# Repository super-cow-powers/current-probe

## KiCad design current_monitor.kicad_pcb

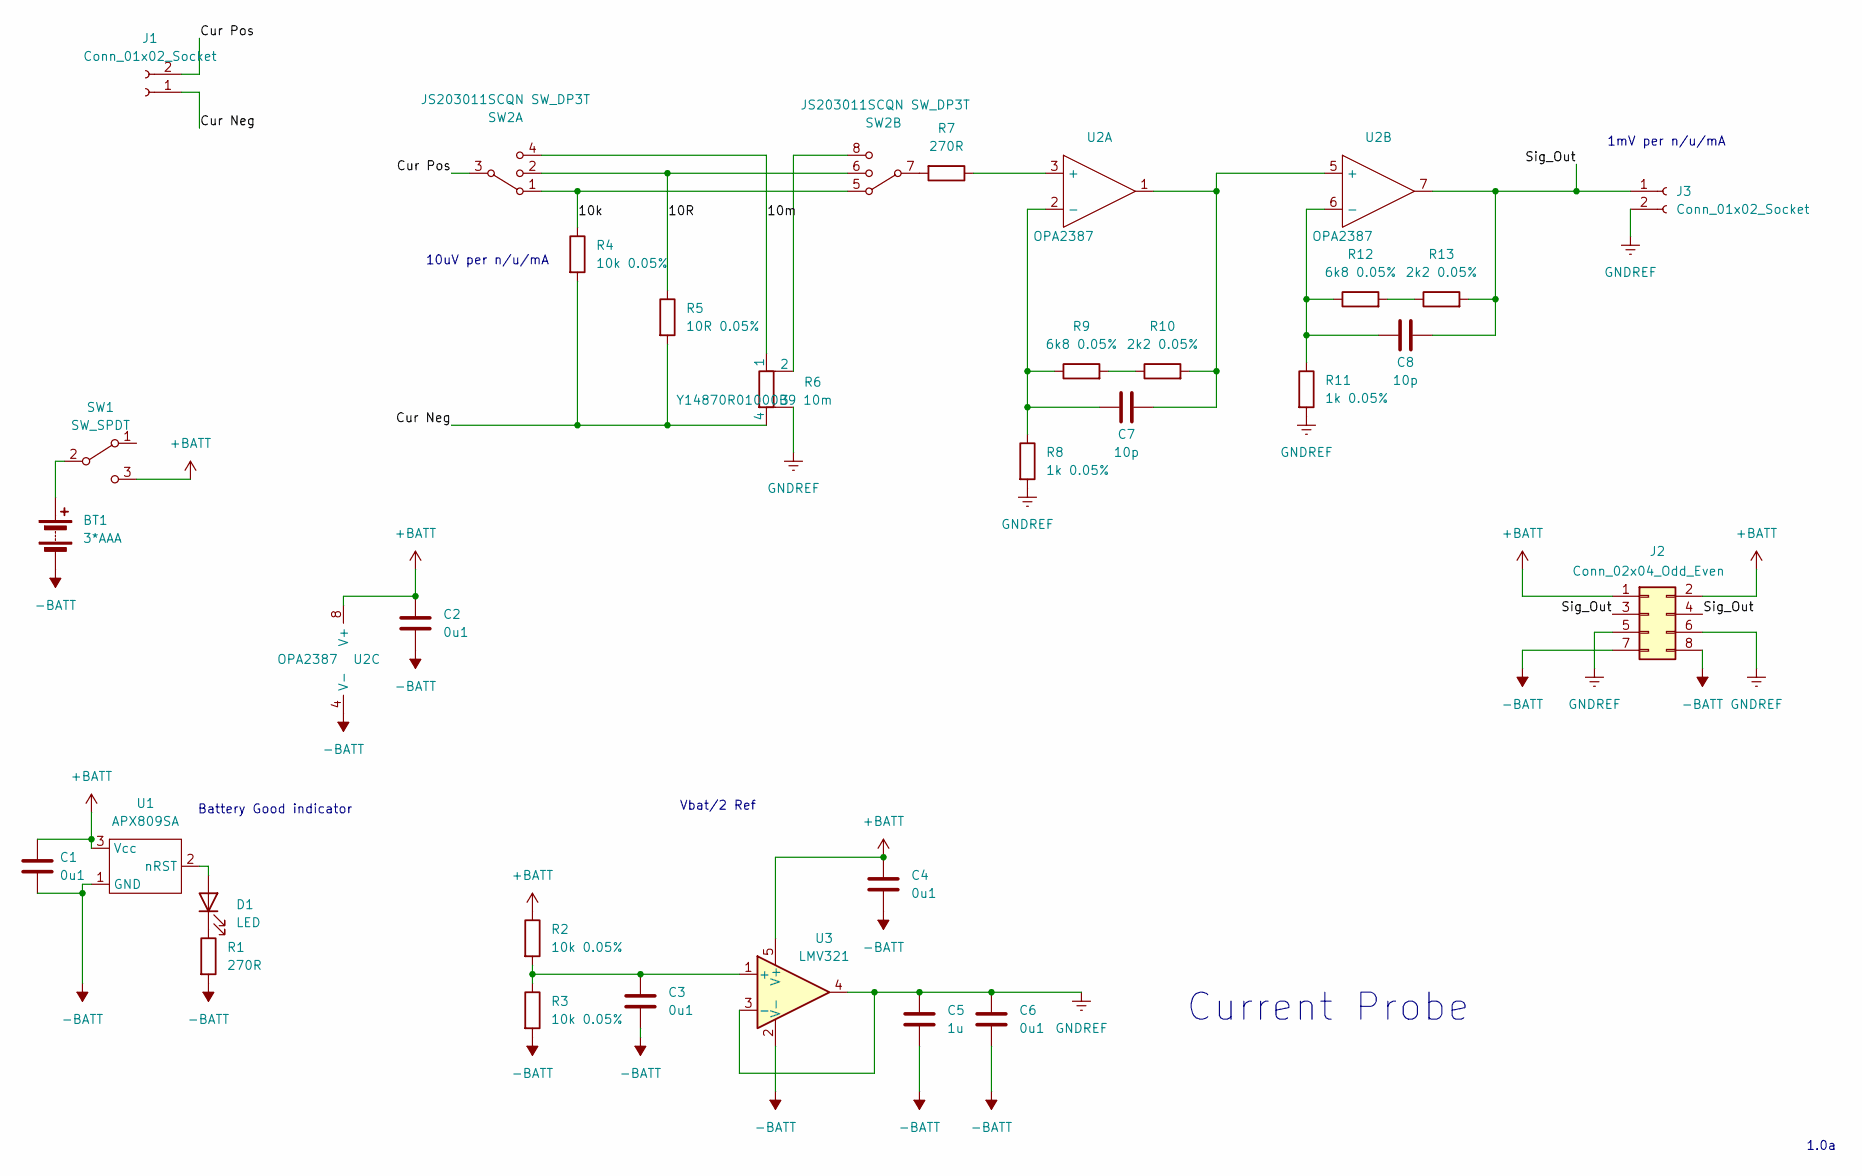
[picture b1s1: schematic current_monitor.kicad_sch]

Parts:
BT1: 3*AAA; PinHeader_1x02_P2.54mm_Vertical
C1, C2, C3, C4, C6: 0u1; C_0603_1608Metric_Pad1.08x0.95mm_HandSolder
C5: 1u; C_0603_1608Metric_Pad1.08x0.95mm_HandSolder
C7, C8: 10p; C_0603_1608Metric_Pad1.08x0.95mm_HandSolder
D1: LED; LED_D3.0mm
J1, J3: Conn_01x02_Socket; Dual M6 Banana
J2: Conn_02x04_Odd_Even; PinHeader_2x04_P1.27mm_Vertical_SMD
R1, R7: 270R; R_0603_1608Metric_Pad0.98x0.95mm_HandSolder
R2, R3, R4: 10k 0.05%; R_1206_3216Metric
R5: 10R 0.05%; R_1206_3216Metric
R6: Y14870R01000B9 10m; CSM2512S
R8, R11: 1k 0.05%; R_1206_3216Metric
R9, R12: 6k8 0.05%; R_1206_3216Metric
R10, R13: 2k2 0.05%; R_1206_3216Metric
SW1: SW_SPDT; SW_Slide_1P2T_CK_OS102011MS2Q
SW2: JS203011SCQN SW_DP3T; JS203011SCQN
U1: APX809SA; SOT-23
U2: OPA2387; VSSOP-8_3.0x3.0mm_P0.65mm
U3: LMV321; SOT-23-5

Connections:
+BATT: C1.1, C2.1, C4.1, J2.1, J2.2, R2.1, SW1.3 (C), U1.3 (Vcc), U2.8 (V+), U3.5 (V+)
-BATT: BT1.2 (-), C1.2, C2.2, C3.2, C4.2, C5.2, C6.2, J2.7, J2.8, R1.2, R3.2, U1.1 (GND), U2.4 (V-), U3.2 (V-)
/10R: R5.1, SW2.2, SW2.6
/10k: R4.1, SW2.1, SW2.5
/10m: R6.1, SW2.4
/Cur Neg: J1.1, R4.2, R5.2, R6.4
/Cur Pos: J1.2, SW2.3
/Sig_Out: C8.2, J2.3, J2.4, J3.1, R13.2, U2.7
GNDREF: C5.1, C6.1, J2.5, J2.6, J3.2, R6.3, R8.2, R11.2, U3.3 (-), U3.4
unnamed: BT1.1 (+), SW1.2 (B)
unnamed: D1.2 (A), U1.2 (nRST)
unnamed: D1.1 (K), R1.1
unnamed: R6.2, SW2.8
unnamed: R7.2, SW2.7
unnamed: R9.2, R10.1
unnamed: R12.2, R13.1
unnamed: R7.1, U2.3 (+)
unnamed: C7.1, R8.1, R9.1, U2.2 (-)
unnamed: C7.2, R10.2, U2.1, U2.5 (+)
unnamed: C8.1, R11.1, R12.1, U2.6 (-)
unnamed: C3.1, R2.2, R3.1, U3.1 (+)

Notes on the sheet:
Battery Good indicator
Vbat/2 Ref
10uV per n/u/mA
Current Probe
1mV per n/u/mA
1.0a

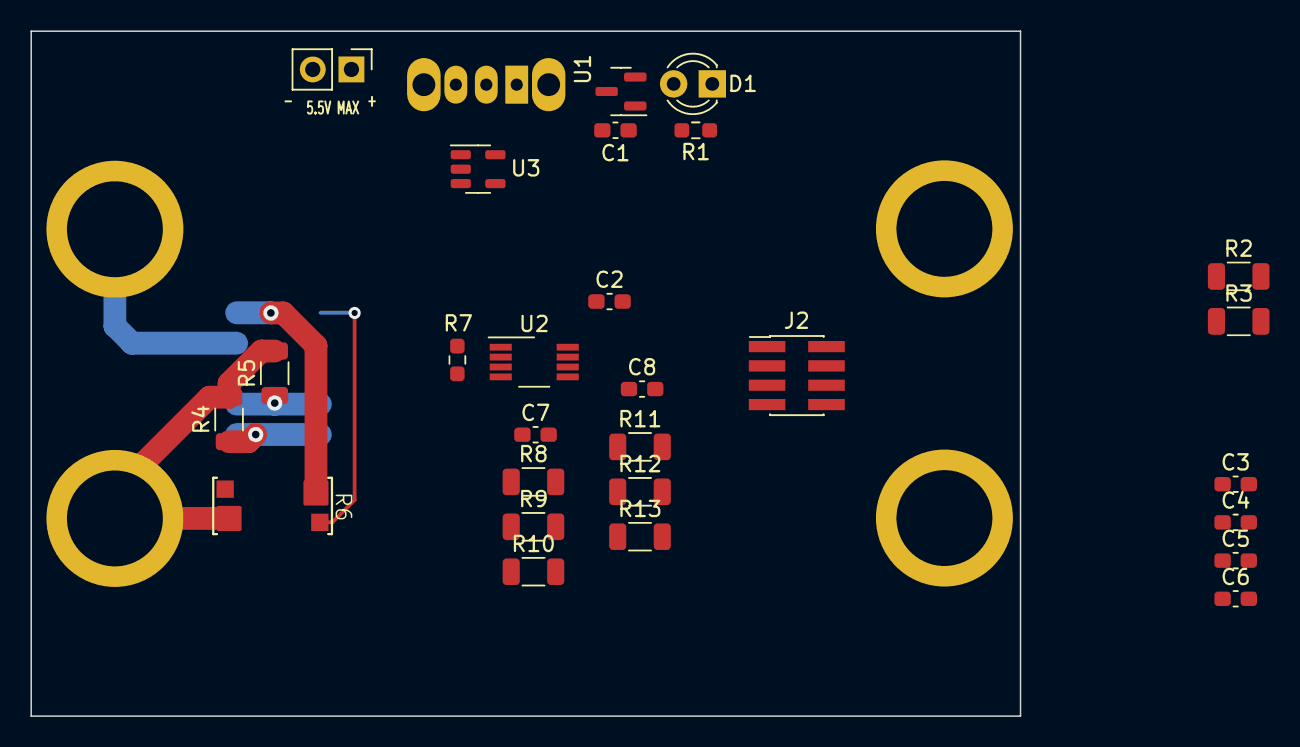
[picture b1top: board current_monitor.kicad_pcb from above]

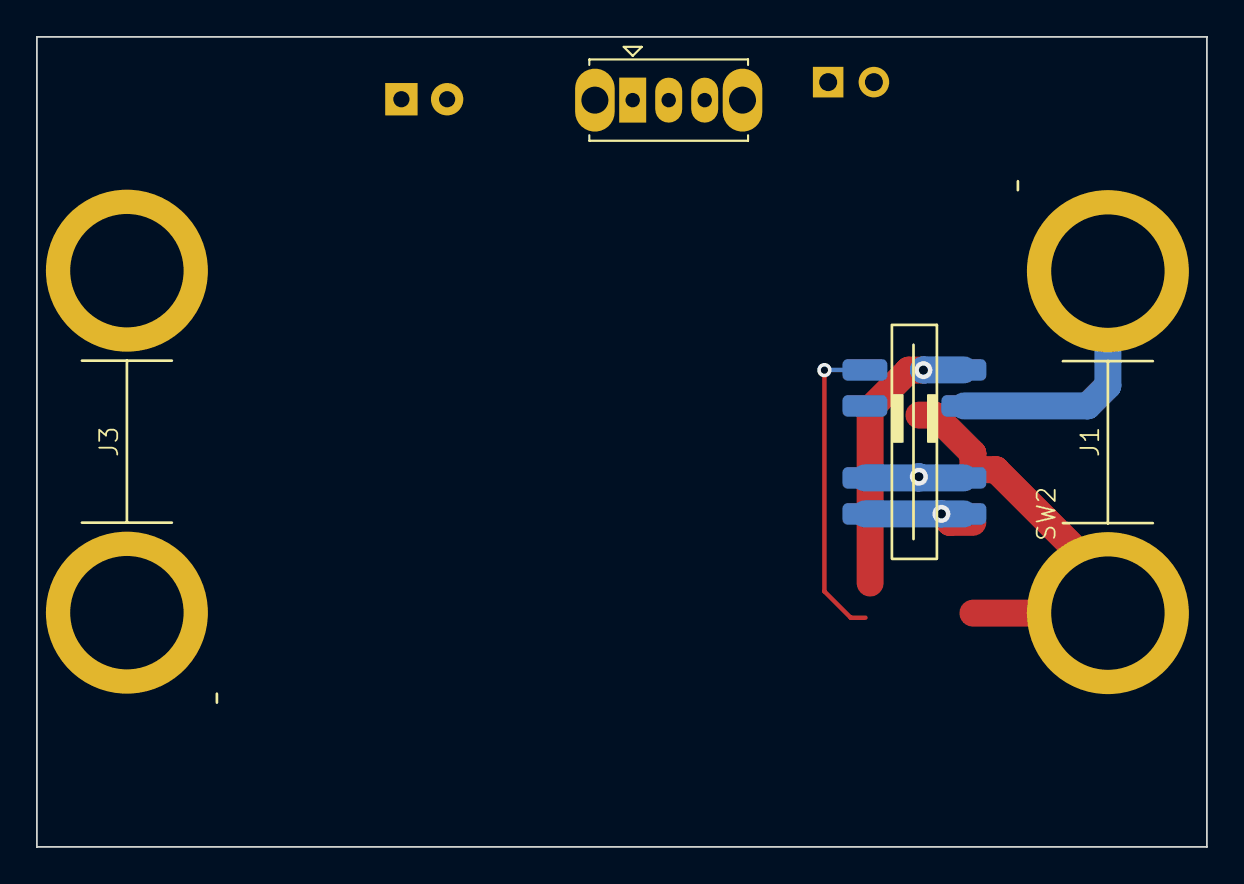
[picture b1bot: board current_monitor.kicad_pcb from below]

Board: 2 copper layers, 65.0 x 45.0 mm, 31 parts (4 on the bottom side), 21 nets.

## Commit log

2023-12-19 Init
